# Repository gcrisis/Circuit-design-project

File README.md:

# 
save my kicad/lceda and others circuit project

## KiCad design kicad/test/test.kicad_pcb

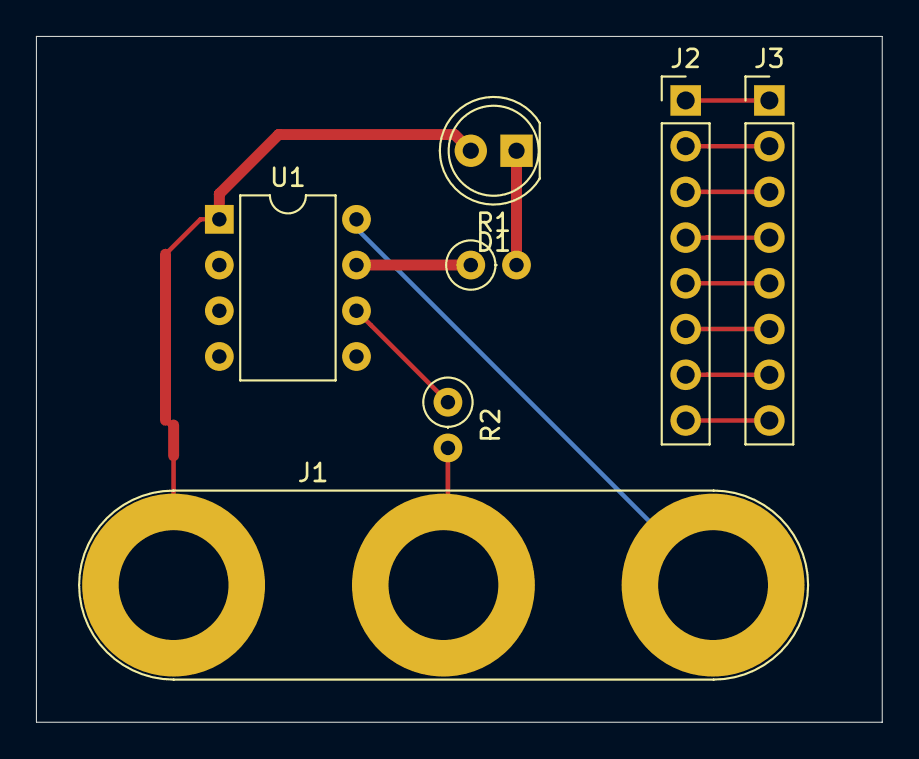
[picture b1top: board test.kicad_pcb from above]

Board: 2 copper layers, 47.0 x 38.1 mm, 7 parts (0 on the bottom side), 14 nets.

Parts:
D1: LED; LED_D5.0mm
J1: myconn3; Banana_Jack_3Pin
J2, J3: Conn_01x08_Male; PinHeader_1x08_P2.54mm_Vertical
R1: 1k; R_Axial_DIN0207_L6.3mm_D2.5mm_P2.54mm_Vertical
R2: 100; R_Axial_DIN0207_L6.3mm_D2.5mm_P2.54mm_Vertical
U1: PIC12C508A-ISN; DIP-8_W7.62mm

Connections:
/a1: J2.1, J3.1
/a2: J2.2, J3.2
/a3: J2.3, J3.3
/a4: J2.4, J3.4
/a5: J2.5, J3.5
/a6: J2.6, J3.6
/a7: J2.7, J3.7
/a8: J2.8, J3.8
/input: R2.1, U1.6
GND: J1.3, U1.8
unnamed: D1.1, R1.2
unnamed: J1.2, R2.2
unnamed: R1.1, U1.7
VCC: D1.2, J1.1, U1.1

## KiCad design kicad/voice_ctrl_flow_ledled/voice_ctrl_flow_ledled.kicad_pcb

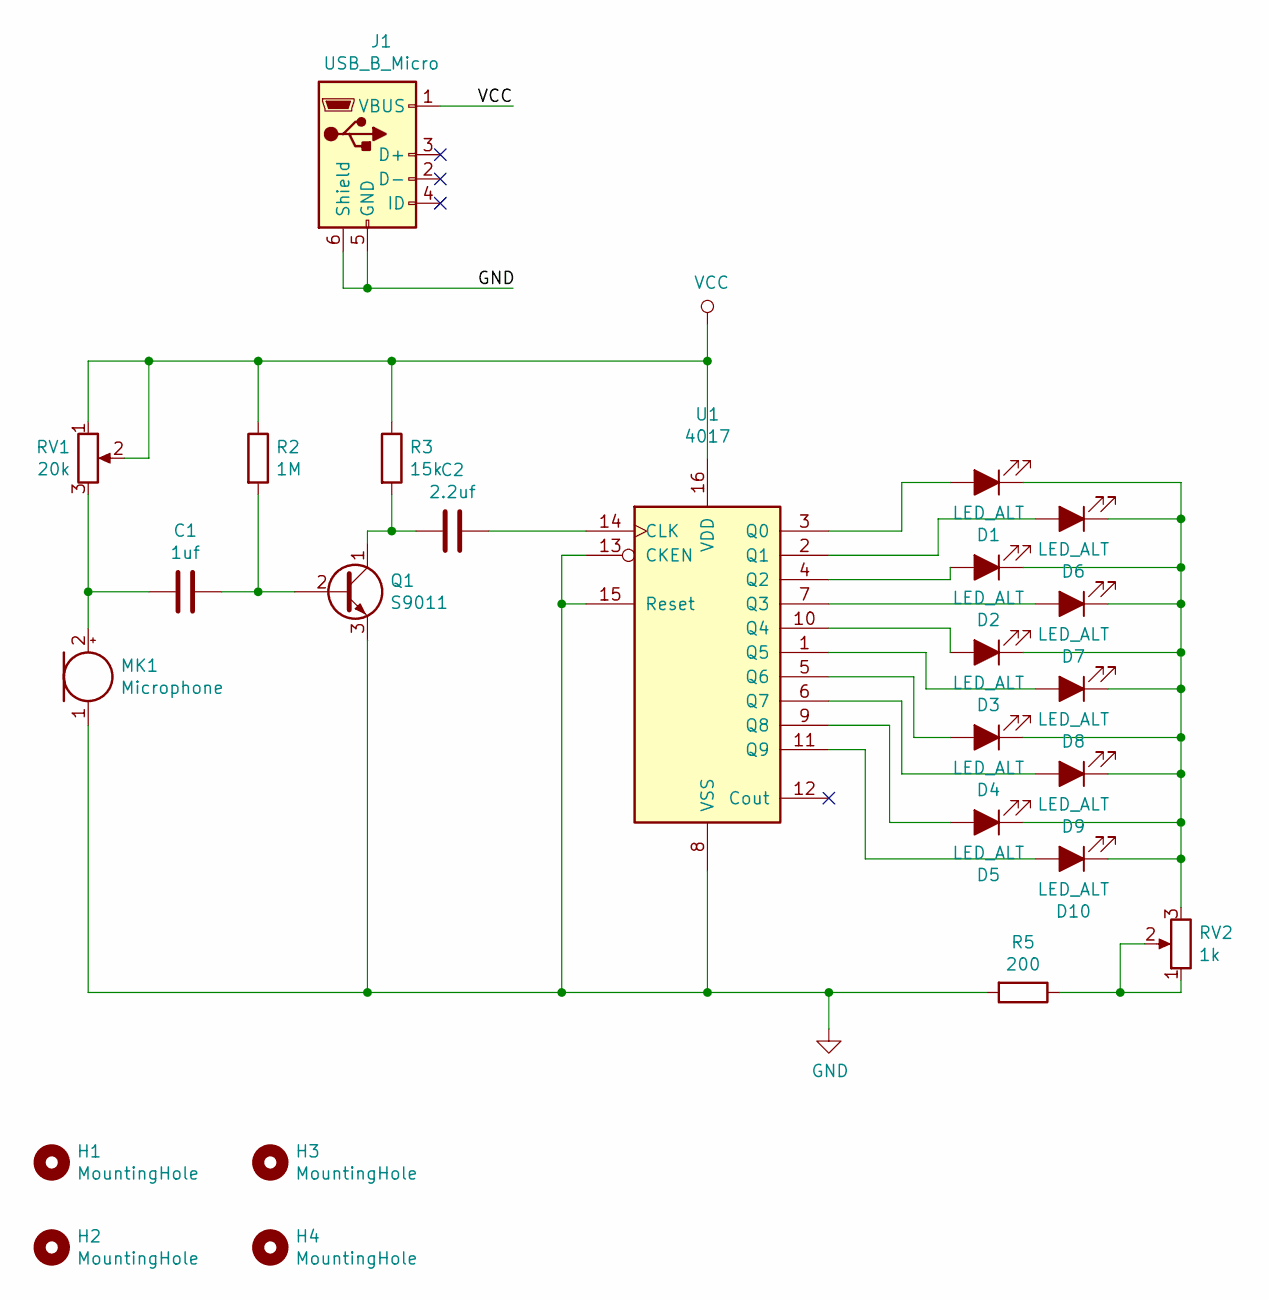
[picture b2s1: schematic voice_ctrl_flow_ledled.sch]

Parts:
C1: 1uf; C_Disc_D3.0mm_W1.6mm_P2.50mm
C2: 2.2uf; C_Disc_D5.0mm_W2.5mm_P2.50mm
D1, D2, D3, D4, D5, D6, D7, D8, D9, D10: LED_ALT; LED_D3.0mm
H1, H2, H3, H4: MountingHole; MountingHole_3.2mm_M3
J1: USB_B_Micro; USB_Micro-B_Molex-105017-0001
MK1: Microphone; CP_Radial_D5.0mm_P2.50mm
Q1: S9011; TO-92
R2: 1M; R_Axial_DIN0204_L3.6mm_D1.6mm_P7.62mm_Horizontal
R3: 15k; R_Axial_DIN0204_L3.6mm_D1.6mm_P7.62mm_Horizontal
R5: 200; R_Axial_DIN0204_L3.6mm_D1.6mm_P5.08mm_Horizontal
RV1: 20k; Potentiometer_Bourns_3296W_Vertical
RV2: 1k; Potentiometer_Bourns_3296W_Vertical
U1: 4017; DIP-16_W7.62mm_LongPads

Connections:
GND: J1.5 (GND), J1.6 (Shield), MK1.1 (-), Q1.3 (E), R5.2, U1.8 (VSS), U1.13 (CKEN), U1.15 (Reset)
unnamed: C1.1, MK1.2 (+), RV1.3
unnamed: C1.2, Q1.2 (B), R2.2
unnamed: C2.1, Q1.1 (C), R3.2
unnamed: C2.2, U1.14 (CLK)
unnamed: D1.1 (K), D2.1 (K), D3.1 (K), D4.1 (K), D5.1 (K), D6.1 (K), D7.1 (K), D8.1 (K), D9.1 (K), D10.1 (K), RV2.3
unnamed: D1.2 (A), U1.3 (Q0)
unnamed: D2.2 (A), U1.4 (Q2)
unnamed: D3.2 (A), U1.10 (Q4)
unnamed: D4.2 (A), U1.5 (Q6)
unnamed: D5.2 (A), U1.9 (Q8)
unnamed: D6.2 (A), U1.2 (Q1)
unnamed: D7.2 (A), U1.7 (Q3)
unnamed: D8.2 (A), U1.1 (Q5)
unnamed: D9.2 (A), U1.6 (Q7)
unnamed: D10.2 (A), U1.11 (Q9)
unnamed: R5.1, RV2.1, RV2.2
VCC: J1.1 (VBUS), R2.1, R3.1, RV1.1, RV1.2, U1.16 (VDD)

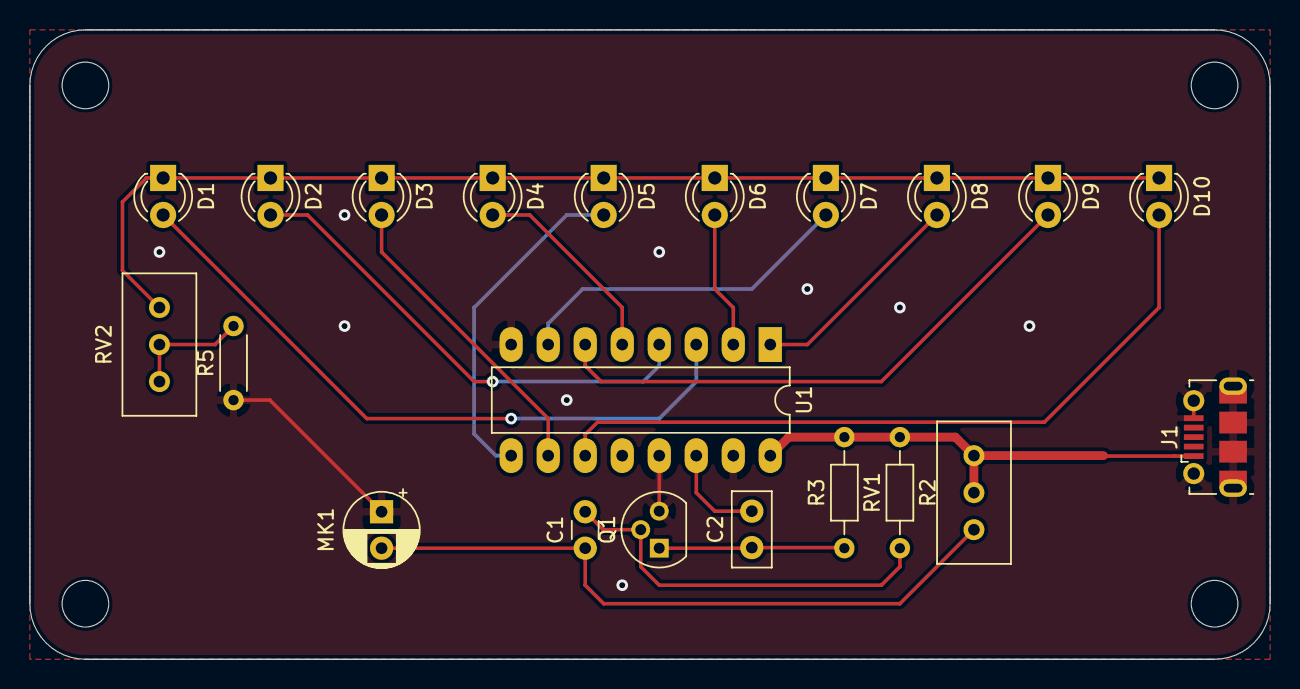
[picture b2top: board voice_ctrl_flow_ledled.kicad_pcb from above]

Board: 2 copper layers, 85.1 x 43.2 mm, 25 parts (0 on the bottom side), 18 nets.

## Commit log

2019-12-25 add files
2021-12-29 add read me under lceda folder
2021-12-29 add lm386 and cube project
